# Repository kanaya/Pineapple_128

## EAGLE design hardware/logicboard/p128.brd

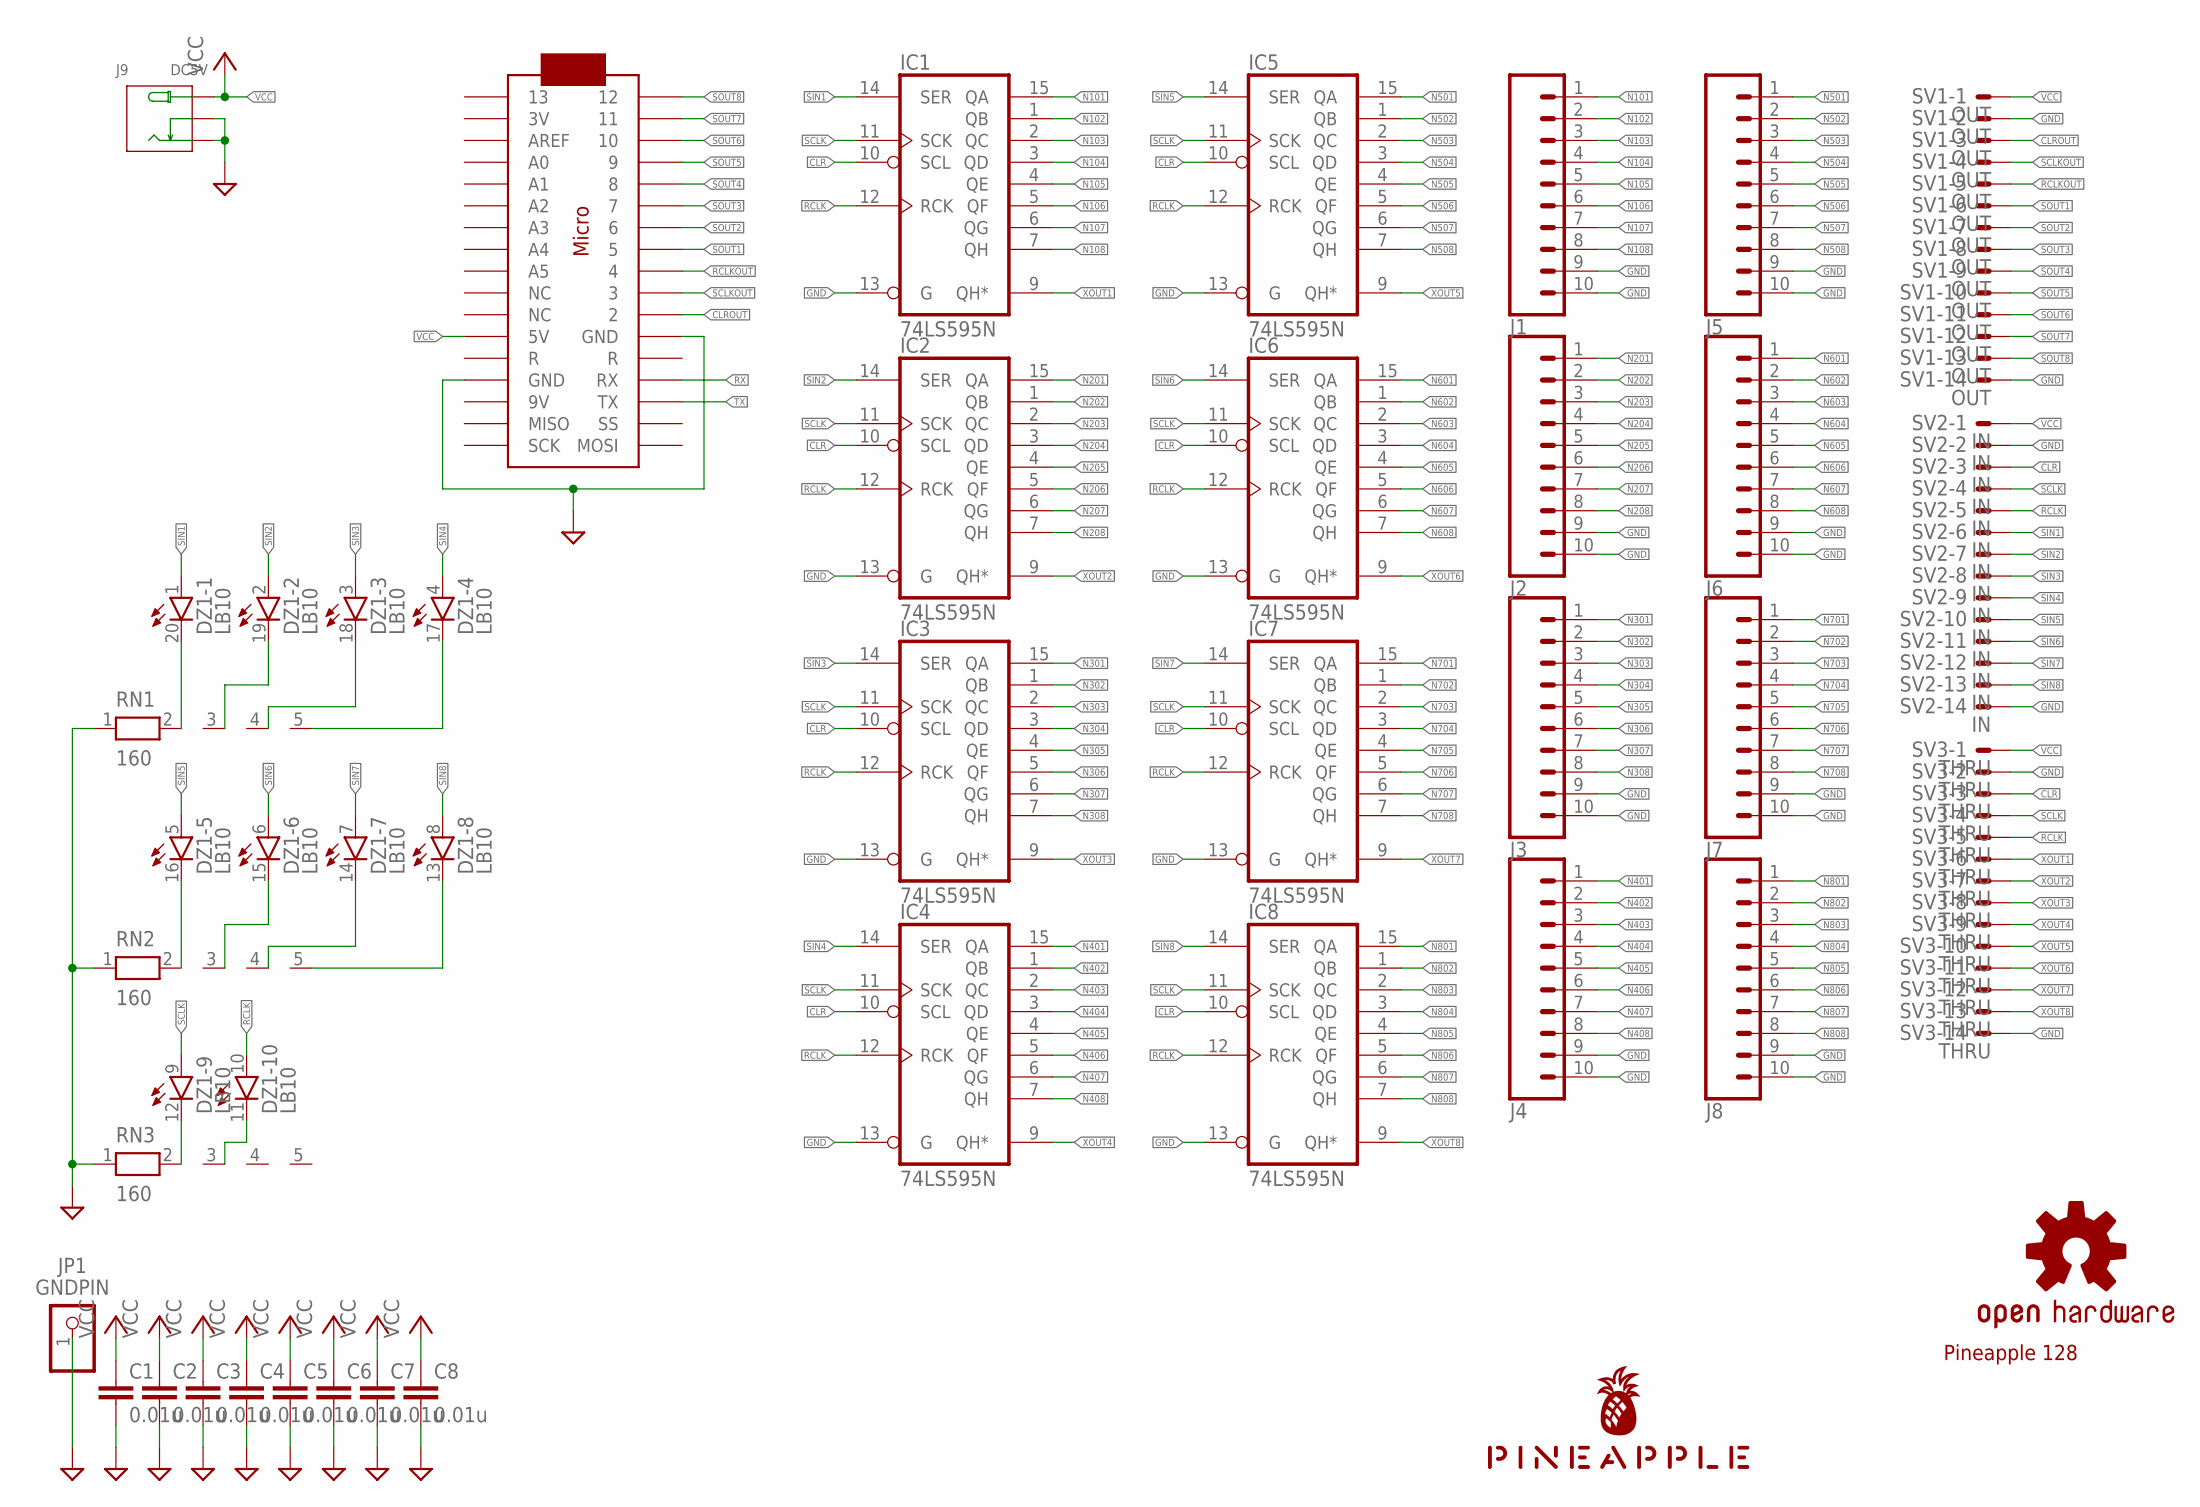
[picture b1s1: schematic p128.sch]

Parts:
C1, C2, C3, C4, C5, C6, C7, C8: 0.01u; C025-024X044
DZ1: LB10
IC1, IC2, IC3, IC4, IC5, IC6, IC7, IC8: 74LS595N; DIL16
J1, J2, J3, J4, J5, J6, J7, J8: CONN_10"; 1X10
J9: DC5V; 3P-L14.2*W11.0*H9.0MM
JP1: GNDPIN; 1X01
LOGO1: OSHW-LOGOS-COPPER; OSHW-LOGO-S_COPPER
RN1, RN2, RN3: 160; RN-5
SV1: OUT; ML14
SV2: IN; ML14
SV3: THRU; ML14
U$1: PINEAPPLE450_SILK
U$2: ARDUINOMICRO

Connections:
CLR: IC1.10 (SCL), IC2.10 (SCL), IC3.10 (SCL), IC4.10 (SCL), IC5.10 (SCL), IC6.10 (SCL), IC7.10 (SCL), IC8.10 (SCL), SV2.3, SV3.3
CLROUT: SV1.3, U$2.P$11 (2)
GND: C1.2, C2.2, C3.2, C4.2, C5.2, C6.2, C7.2, C8.2, IC1.8 (GND), IC1.13 (G), IC2.8 (GND), IC2.13 (G), IC3.8 (GND), IC3.13 (G), IC4.8 (GND), IC4.13 (G), IC5.8 (GND), IC5.13 (G), IC6.8 (GND), IC6.13 (G), IC7.8 (GND), IC7.13 (G), IC8.8 (GND), IC8.13 (G), J1.9, J1.10, J2.9, J2.10, J3.9, J3.10, J4.9, J4.10, J5.9, J5.10, J6.9, J6.10, J7.9, J7.10, J8.9, J8.10, J9.-1 (-), J9.-2 (CDN), JP1.1, RN1.1, RN2.1, RN3.1, SV1.2, SV1.14, SV2.2, SV2.14, SV3.2, SV3.14, U$2.P$12 (GND), U$2.P$21 (GND)
N101: IC1.15 (QA), J1.1
N102: IC1.1 (QB), J1.2
N103: IC1.2 (QC), J1.3
N104: IC1.3 (QD), J1.4
N105: IC1.4 (QE), J1.5
N106: IC1.5 (QF), J1.6
N107: IC1.6 (QG), J1.7
N108: IC1.7 (QH), J1.8
N201: IC2.15 (QA), J2.1
N202: IC2.1 (QB), J2.2
N203: IC2.2 (QC), J2.3
N204: IC2.3 (QD), J2.4
N205: IC2.4 (QE), J2.5
N206: IC2.5 (QF), J2.6
N207: IC2.6 (QG), J2.7
N208: IC2.7 (QH), J2.8
N301: IC3.15 (QA), J3.1
N302: IC3.1 (QB), J3.2
N303: IC3.2 (QC), J3.3
N304: IC3.3 (QD), J3.4
N305: IC3.4 (QE), J3.5
N306: IC3.5 (QF), J3.6
N307: IC3.6 (QG), J3.7
N308: IC3.7 (QH), J3.8
N401: IC4.15 (QA), J4.1
N402: IC4.1 (QB), J4.2
N403: IC4.2 (QC), J4.3
N404: IC4.3 (QD), J4.4
N405: IC4.4 (QE), J4.5
N406: IC4.5 (QF), J4.6
N407: IC4.6 (QG), J4.7
N408: IC4.7 (QH), J4.8
N501: IC5.15 (QA), J5.1
N502: IC5.1 (QB), J5.2
N503: IC5.2 (QC), J5.3
N504: IC5.3 (QD), J5.4
N505: IC5.4 (QE), J5.5
N506: IC5.5 (QF), J5.6
N507: IC5.6 (QG), J5.7
N508: IC5.7 (QH), J5.8
N601: IC6.15 (QA), J6.1
N602: IC6.1 (QB), J6.2
N603: IC6.2 (QC), J6.3
N604: IC6.3 (QD), J6.4
N605: IC6.4 (QE), J6.5
N606: IC6.5 (QF), J6.6
N607: IC6.6 (QG), J6.7
N608: IC6.7 (QH), J6.8
N701: IC7.15 (QA), J7.1
N702: IC7.1 (QB), J7.2
N703: IC7.2 (QC), J7.3
N704: IC7.3 (QD), J7.4
N705: IC7.4 (QE), J7.5
N706: IC7.5 (QF), J7.6
N707: IC7.6 (QG), J7.7
N708: IC7.7 (QH), J7.8
N801: IC8.15 (QA), J8.1
N802: IC8.1 (QB), J8.2
N803: IC8.2 (QC), J8.3
N804: IC8.3 (QD), J8.4
N805: IC8.4 (QE), J8.5
N806: IC8.5 (QF), J8.6
N807: IC8.6 (QG), J8.7
N808: IC8.7 (QH), J8.8
unnamed: DZ1.20 (C), RN1.2
unnamed: DZ1.19 (C), RN1.3
unnamed: DZ1.18 (C), RN1.4
unnamed: DZ1.17 (C), RN1.5
unnamed: DZ1.16 (C), RN2.2
unnamed: DZ1.15 (C), RN2.3
unnamed: DZ1.14 (C), RN2.4
unnamed: DZ1.13 (C), RN2.5
unnamed: DZ1.12 (C), RN3.2
unnamed: DZ1.11 (C), RN3.3
RCLK: DZ1.10 (A), IC1.12 (RCK), IC2.12 (RCK), IC3.12 (RCK), IC4.12 (RCK), IC5.12 (RCK), IC6.12 (RCK), IC7.12 (RCK), IC8.12 (RCK), SV2.5, SV3.5
RCLKOUT: SV1.5, U$2.P$9 (4)
RX: U$2.P$14 (RX)
SCLK: DZ1.9 (A), IC1.11 (SCK), IC2.11 (SCK), IC3.11 (SCK), IC4.11 (SCK), IC5.11 (SCK), IC6.11 (SCK), IC7.11 (SCK), IC8.11 (SCK), SV2.4, SV3.4
SCLKOUT: SV1.4, U$2.P$10 (3)
SIN1: DZ1.1 (A), IC1.14 (SER), SV2.6
SIN2: DZ1.2 (A), IC2.14 (SER), SV2.7
SIN3: DZ1.3 (A), IC3.14 (SER), SV2.8
SIN4: DZ1.4 (A), IC4.14 (SER), SV2.9
SIN5: DZ1.5 (A), IC5.14 (SER), SV2.10
SIN6: DZ1.6 (A), IC6.14 (SER), SV2.11
SIN7: DZ1.7 (A), IC7.14 (SER), SV2.12
SIN8: DZ1.8 (A), IC8.14 (SER), SV2.13
SOUT1: SV1.6, U$2.P$8 (5)
SOUT2: SV1.7, U$2.P$7 (6)
SOUT3: SV1.8, U$2.P$6 (7)
SOUT4: SV1.9, U$2.P$5 (8)
SOUT5: SV1.10, U$2.P$4 (9)
SOUT6: SV1.11, U$2.P$3 (10)
SOUT7: SV1.12, U$2.P$2 (11)
SOUT8: SV1.13, U$2.P$1 (12)
TX: U$2.P$15 (TX)
VCC: C1.1, C2.1, C3.1, C4.1, C5.1, C6.1, C7.1, C8.1, IC1.16 (VCC), IC2.16 (VCC), IC3.16 (VCC), IC4.16 (VCC), IC5.16 (VCC), IC6.16 (VCC), IC7.16 (VCC), IC8.16 (VCC), J9.+, SV1.1, SV2.1, SV3.1, U$2.P$23 (5V)
XOUT1: IC1.9 (QH*), SV3.6
XOUT2: IC2.9 (QH*), SV3.7
XOUT3: IC3.9 (QH*), SV3.8
XOUT4: IC4.9 (QH*), SV3.9
XOUT5: IC5.9 (QH*), SV3.10
XOUT6: IC6.9 (QH*), SV3.11
XOUT7: IC7.9 (QH*), SV3.12
XOUT8: IC8.9 (QH*), SV3.13

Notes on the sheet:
Pineapple 128

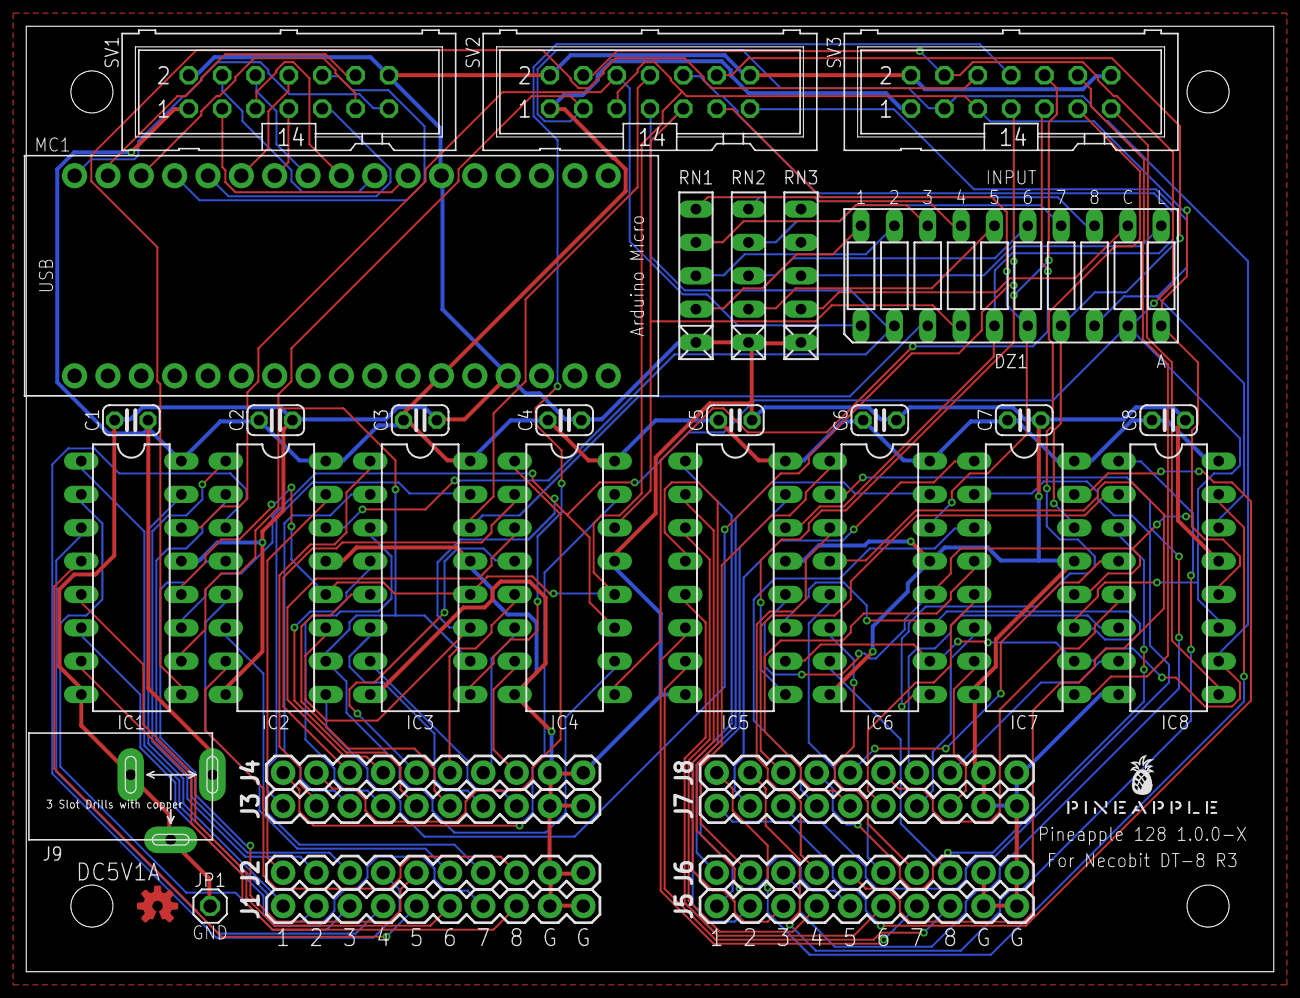
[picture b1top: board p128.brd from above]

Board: 2 copper layers, 94.9 x 71.9 mm, 36 parts (0 on the bottom side), 106 nets.

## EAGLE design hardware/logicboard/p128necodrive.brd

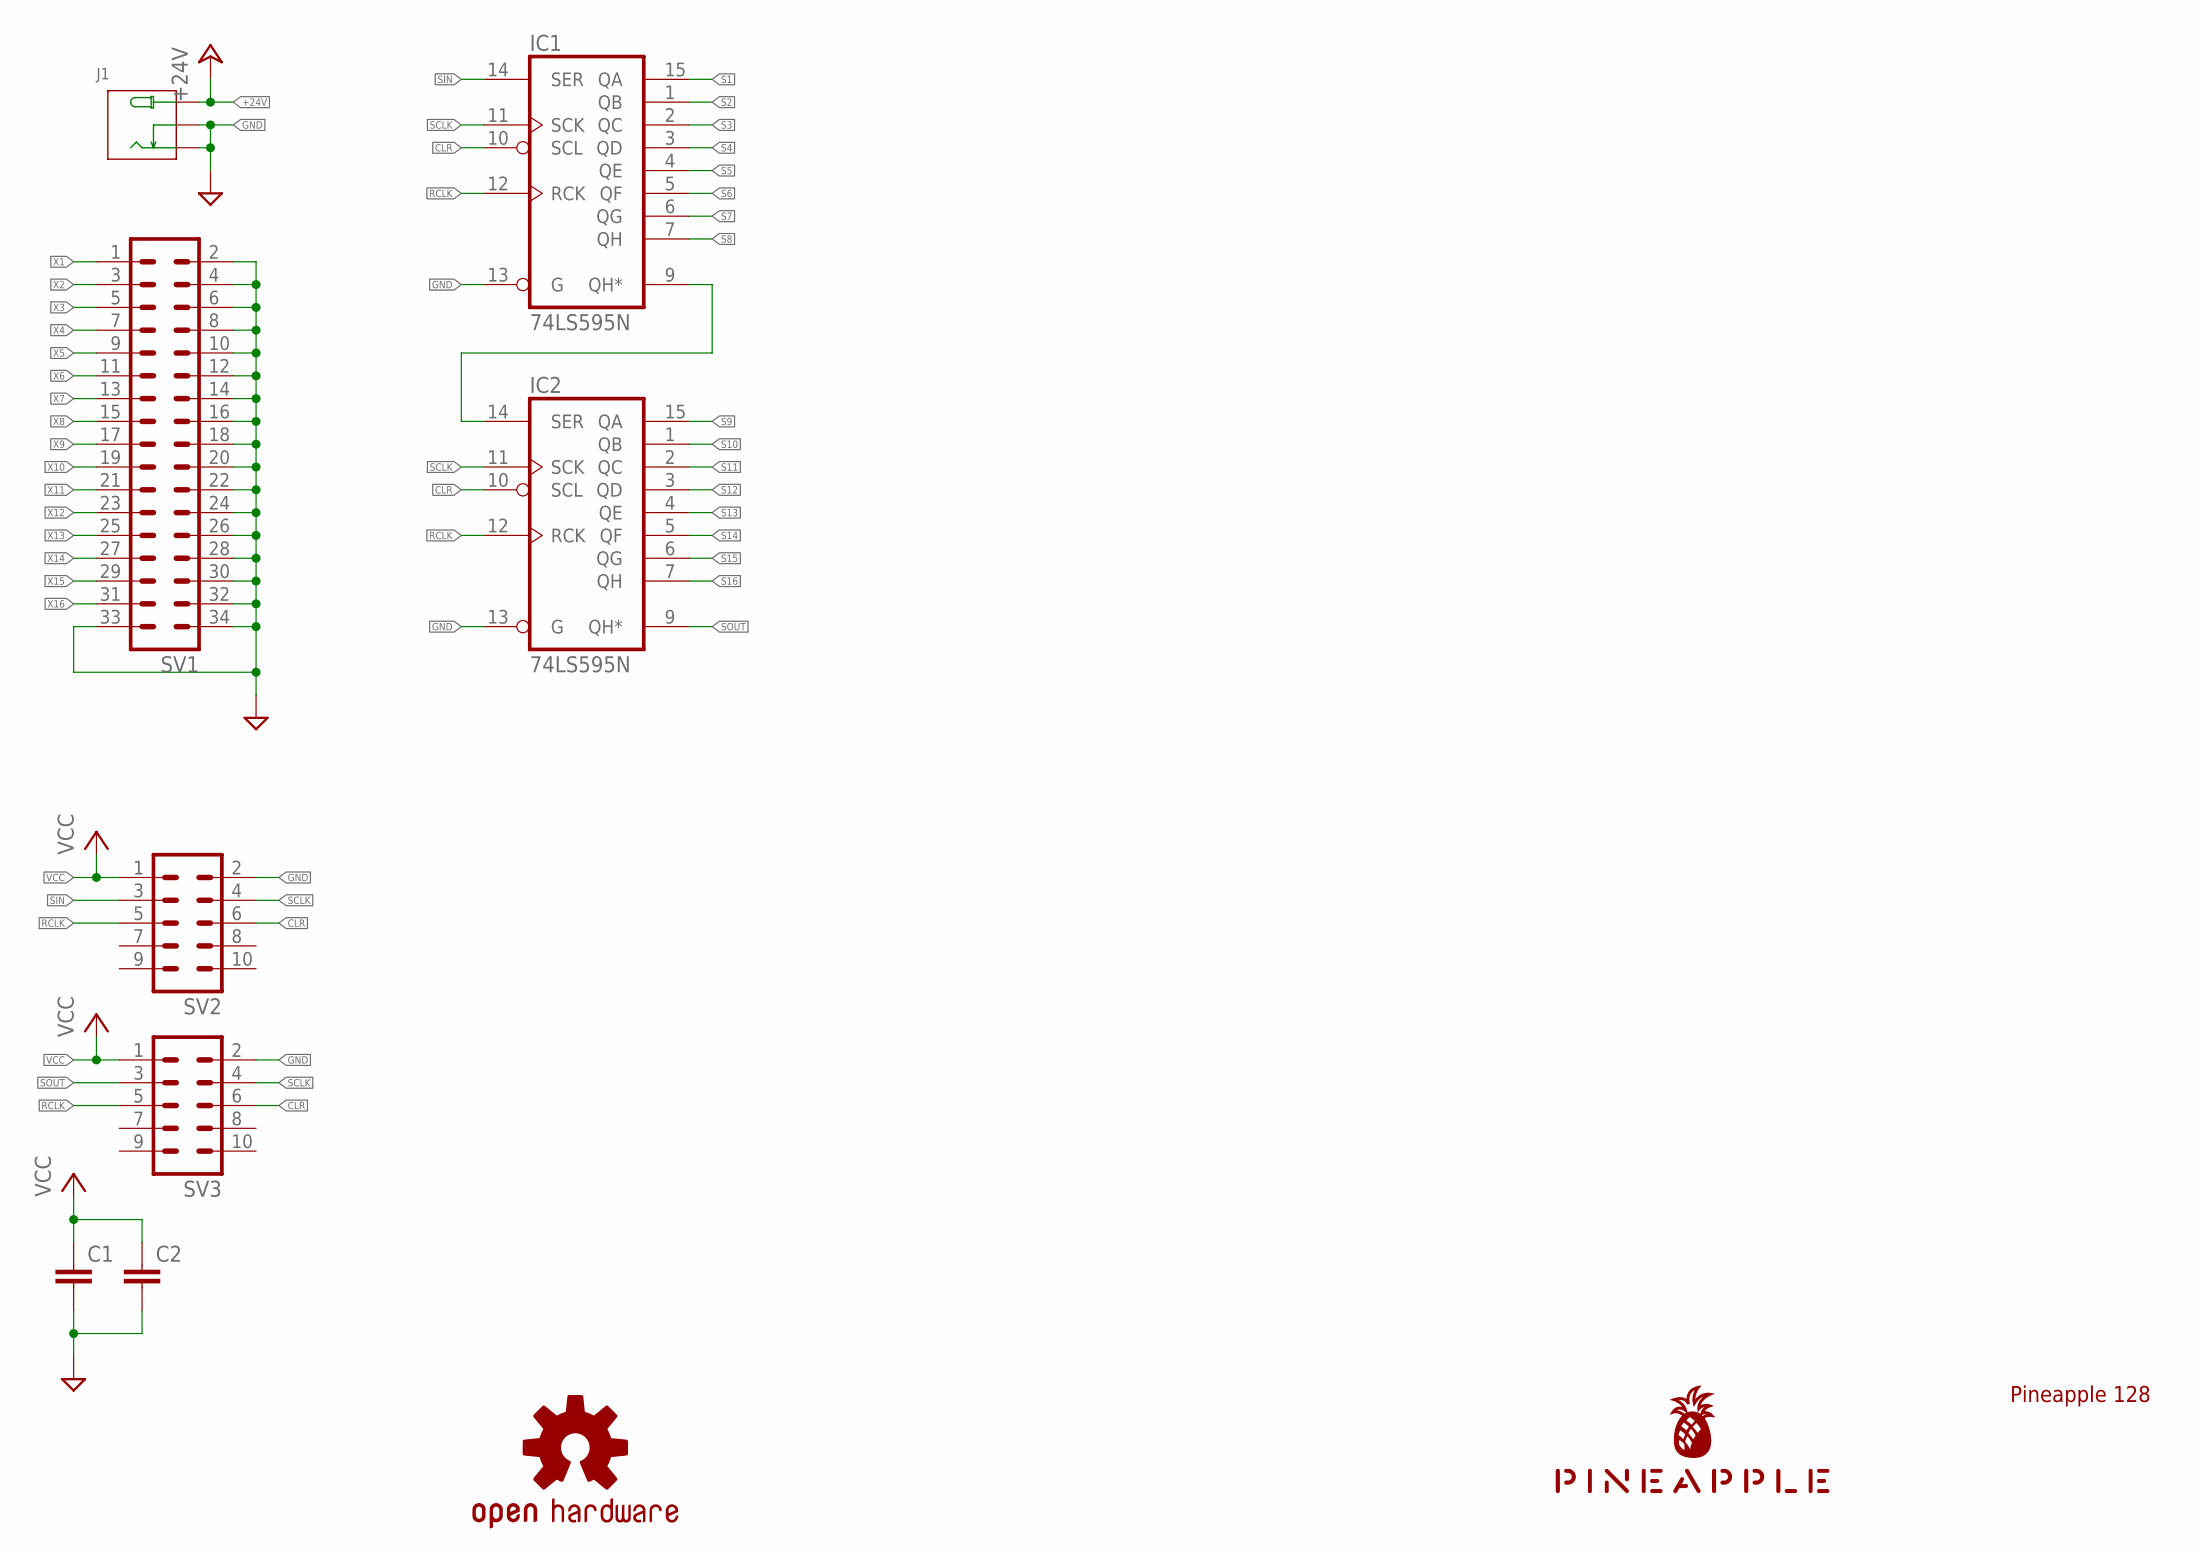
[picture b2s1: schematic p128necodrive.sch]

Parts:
C1, C2: C-EU025-024X044; C025-024X044
IC1, IC2: 74LS595N; DIL16
J1: JACK-DC-005'DC-005'; 3P-L14.2*W11.0*H9.0MM
LOGO1: OSHW-LOGOS-COPPER; OSHW-LOGO-S_COPPER
SV1: ML34L
SV2, SV3: ML10L
U$1: PINEAPPLE450_SILK

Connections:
+24V: J1.+
CLR: IC1.10 (SCL), IC2.10 (SCL), SV2.6, SV3.6
GND: C1.2, C2.2, IC1.8 (GND), IC1.13 (G), IC2.8 (GND), IC2.13 (G), J1.-1 (-), J1.-2 (CDN), SV1.2, SV1.4, SV1.6, SV1.8, SV1.10, SV1.12, SV1.14, SV1.16, SV1.18, SV1.20, SV1.22, SV1.24, SV1.26, SV1.28, SV1.30, SV1.32, SV1.33, SV1.34, SV2.2, SV3.2
unnamed: IC1.9 (QH*), IC2.14 (SER)
RCLK: IC1.12 (RCK), IC2.12 (RCK), SV2.5, SV3.5
S1: IC1.15 (QA)
S2: IC1.1 (QB)
S3: IC1.2 (QC)
S4: IC1.3 (QD)
S5: IC1.4 (QE)
S6: IC1.5 (QF)
S7: IC1.6 (QG)
S8: IC1.7 (QH)
S9: IC2.15 (QA)
S10: IC2.1 (QB)
S11: IC2.2 (QC)
S12: IC2.3 (QD)
S13: IC2.4 (QE)
S14: IC2.5 (QF)
S15: IC2.6 (QG)
S16: IC2.7 (QH)
SCLK: IC1.11 (SCK), IC2.11 (SCK), SV2.4, SV3.4
SIN: IC1.14 (SER), SV2.3
SOUT: IC2.9 (QH*), SV3.3
VCC: C1.1, C2.1, IC1.16 (VCC), IC2.16 (VCC), SV2.1, SV3.1
X1: SV1.1
X2: SV1.3
X3: SV1.5
X4: SV1.7
X5: SV1.9
X6: SV1.11
X7: SV1.13
X8: SV1.15
X9: SV1.17
X10: SV1.19
X11: SV1.21
X12: SV1.23
X13: SV1.25
X14: SV1.27
X15: SV1.29
X16: SV1.31

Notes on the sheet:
Pineapple 128

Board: 2 copper layers, 10 parts (0 on the bottom side), 8 nets, no tracks yet.

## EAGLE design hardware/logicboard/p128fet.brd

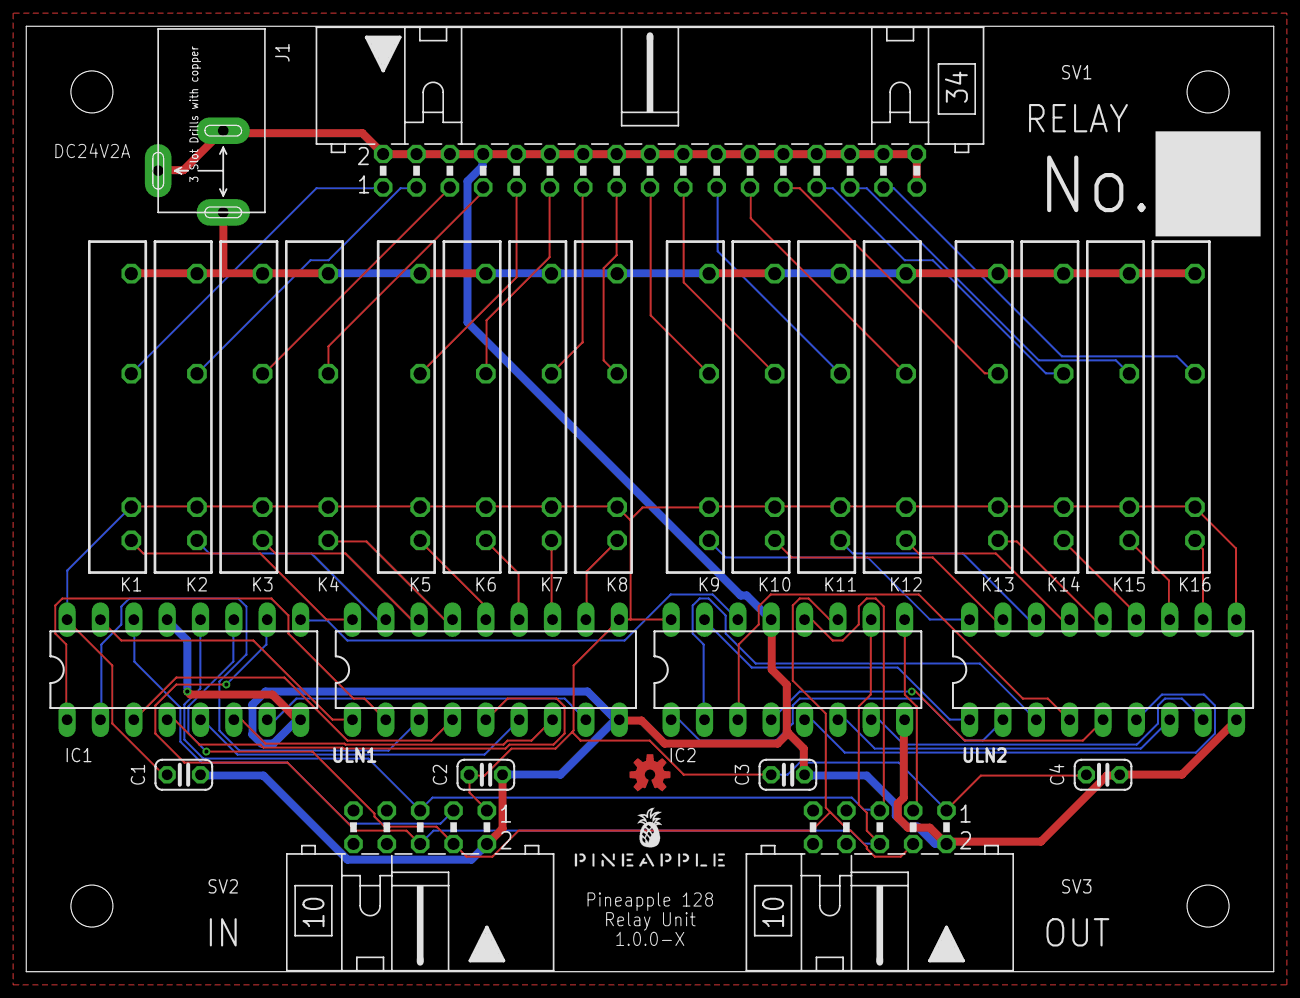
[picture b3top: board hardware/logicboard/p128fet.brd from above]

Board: 2 copper layers, 94.9 x 71.9 mm, 30 parts (0 on the bottom side), 57 nets.

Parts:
C1, C2, C3, C4: C025-024X044
IC1, IC2: 74LS595N; DIL16
J1: 3P-L14.2*W11.0*H9.0MM
K1, K2, K3, K4, K5, K6, K7, K8, K9, K10, K11, K12, K13, K14, K15, K16: AQG12105; AQG
LOGO1: OSHW-LOGOS-COPPER; OSHW-LOGO-S_COPPER
SV1: ML34L
SV2, SV3: ML10L
U$1: PINEAPPLE450_SILK
ULN1, ULN2: DIL18

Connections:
+24V: J1.+, K1.O2, K2.O2, K3.O2, K4.O2, K5.O2, K6.O2, K7.O2, K8.O2, K9.O2, K10.O2, K11.O2, K12.O2, K13.O2, K14.O2, K15.O2, K16.O2
CLR: IC1.10, IC2.10, SV2.6, SV3.6
GND: C1.2, C2.2, C3.2, C4.2, IC1.8, IC1.13, IC2.8, IC2.13, J1.-1, J1.-2, SV1.2, SV1.4, SV1.6, SV1.8, SV1.10, SV1.12, SV1.14, SV1.16, SV1.18, SV1.20, SV1.22, SV1.24, SV1.26, SV1.28, SV1.30, SV1.32, SV1.33, SV1.34, SV2.2, SV3.2, ULN1.9, ULN2.9
unnamed: IC1.9, IC2.14
R1: K1.-, ULN1.18
R2: K2.-, ULN1.17
R3: K3.-, ULN1.16
R4: K4.-, ULN1.15
R5: K5.-, ULN1.14
R6: K6.-, ULN1.13
R7: K7.-, ULN1.12
R8: K8.-, ULN1.11
R9: K9.-, ULN2.18
R10: K10.-, ULN2.17
R11: K11.-, ULN2.16
R12: K12.-, ULN2.15
R13: K13.-, ULN2.14
R14: K14.-, ULN2.13
R15: K15.-, ULN2.12
R16: K16.-, ULN2.11
RCLK: IC1.12, IC2.12, SV2.5, SV3.5
S1: IC1.15, ULN1.1
S2: IC1.1, ULN1.2
S3: IC1.2, ULN1.3
S4: IC1.3, ULN1.4
S5: IC1.4, ULN1.5
S6: IC1.5, ULN1.6
S7: IC1.6, ULN1.7
S8: IC1.7, ULN1.8
S9: IC2.15, ULN2.1
S10: IC2.1, ULN2.2
S11: IC2.2, ULN2.3
S12: IC2.3, ULN2.4
S13: IC2.4, ULN2.5
S14: IC2.5, ULN2.6
S15: IC2.6, ULN2.7
S16: IC2.7, ULN2.8
SCLK: IC1.11, IC2.11, SV2.4, SV3.4
SIN: IC1.14, SV2.3
SOUT: IC2.9, SV3.3
VCC: C1.1, C2.1, C3.1, C4.1, IC1.16, IC2.16, K1.+, K2.+, K3.+, K4.+, K5.+, K6.+, K7.+, K8.+, K9.+, K10.+, K11.+, K12.+, K13.+, K14.+, K15.+, K16.+, SV2.1, SV3.1, ULN1.10, ULN2.10
X1: K1.O1, SV1.1
X2: K2.O1, SV1.3
X3: K3.O1, SV1.5
X4: K4.O1, SV1.7
X5: K5.O1, SV1.9
X6: K6.O1, SV1.11
X7: K7.O1, SV1.13
X8: K8.O1, SV1.15
X9: K9.O1, SV1.17
X10: K10.O1, SV1.19
X11: K11.O1, SV1.21
X12: K12.O1, SV1.23
X13: K13.O1, SV1.25
X14: K14.O1, SV1.27
X15: K15.O1, SV1.29
X16: K16.O1, SV1.31

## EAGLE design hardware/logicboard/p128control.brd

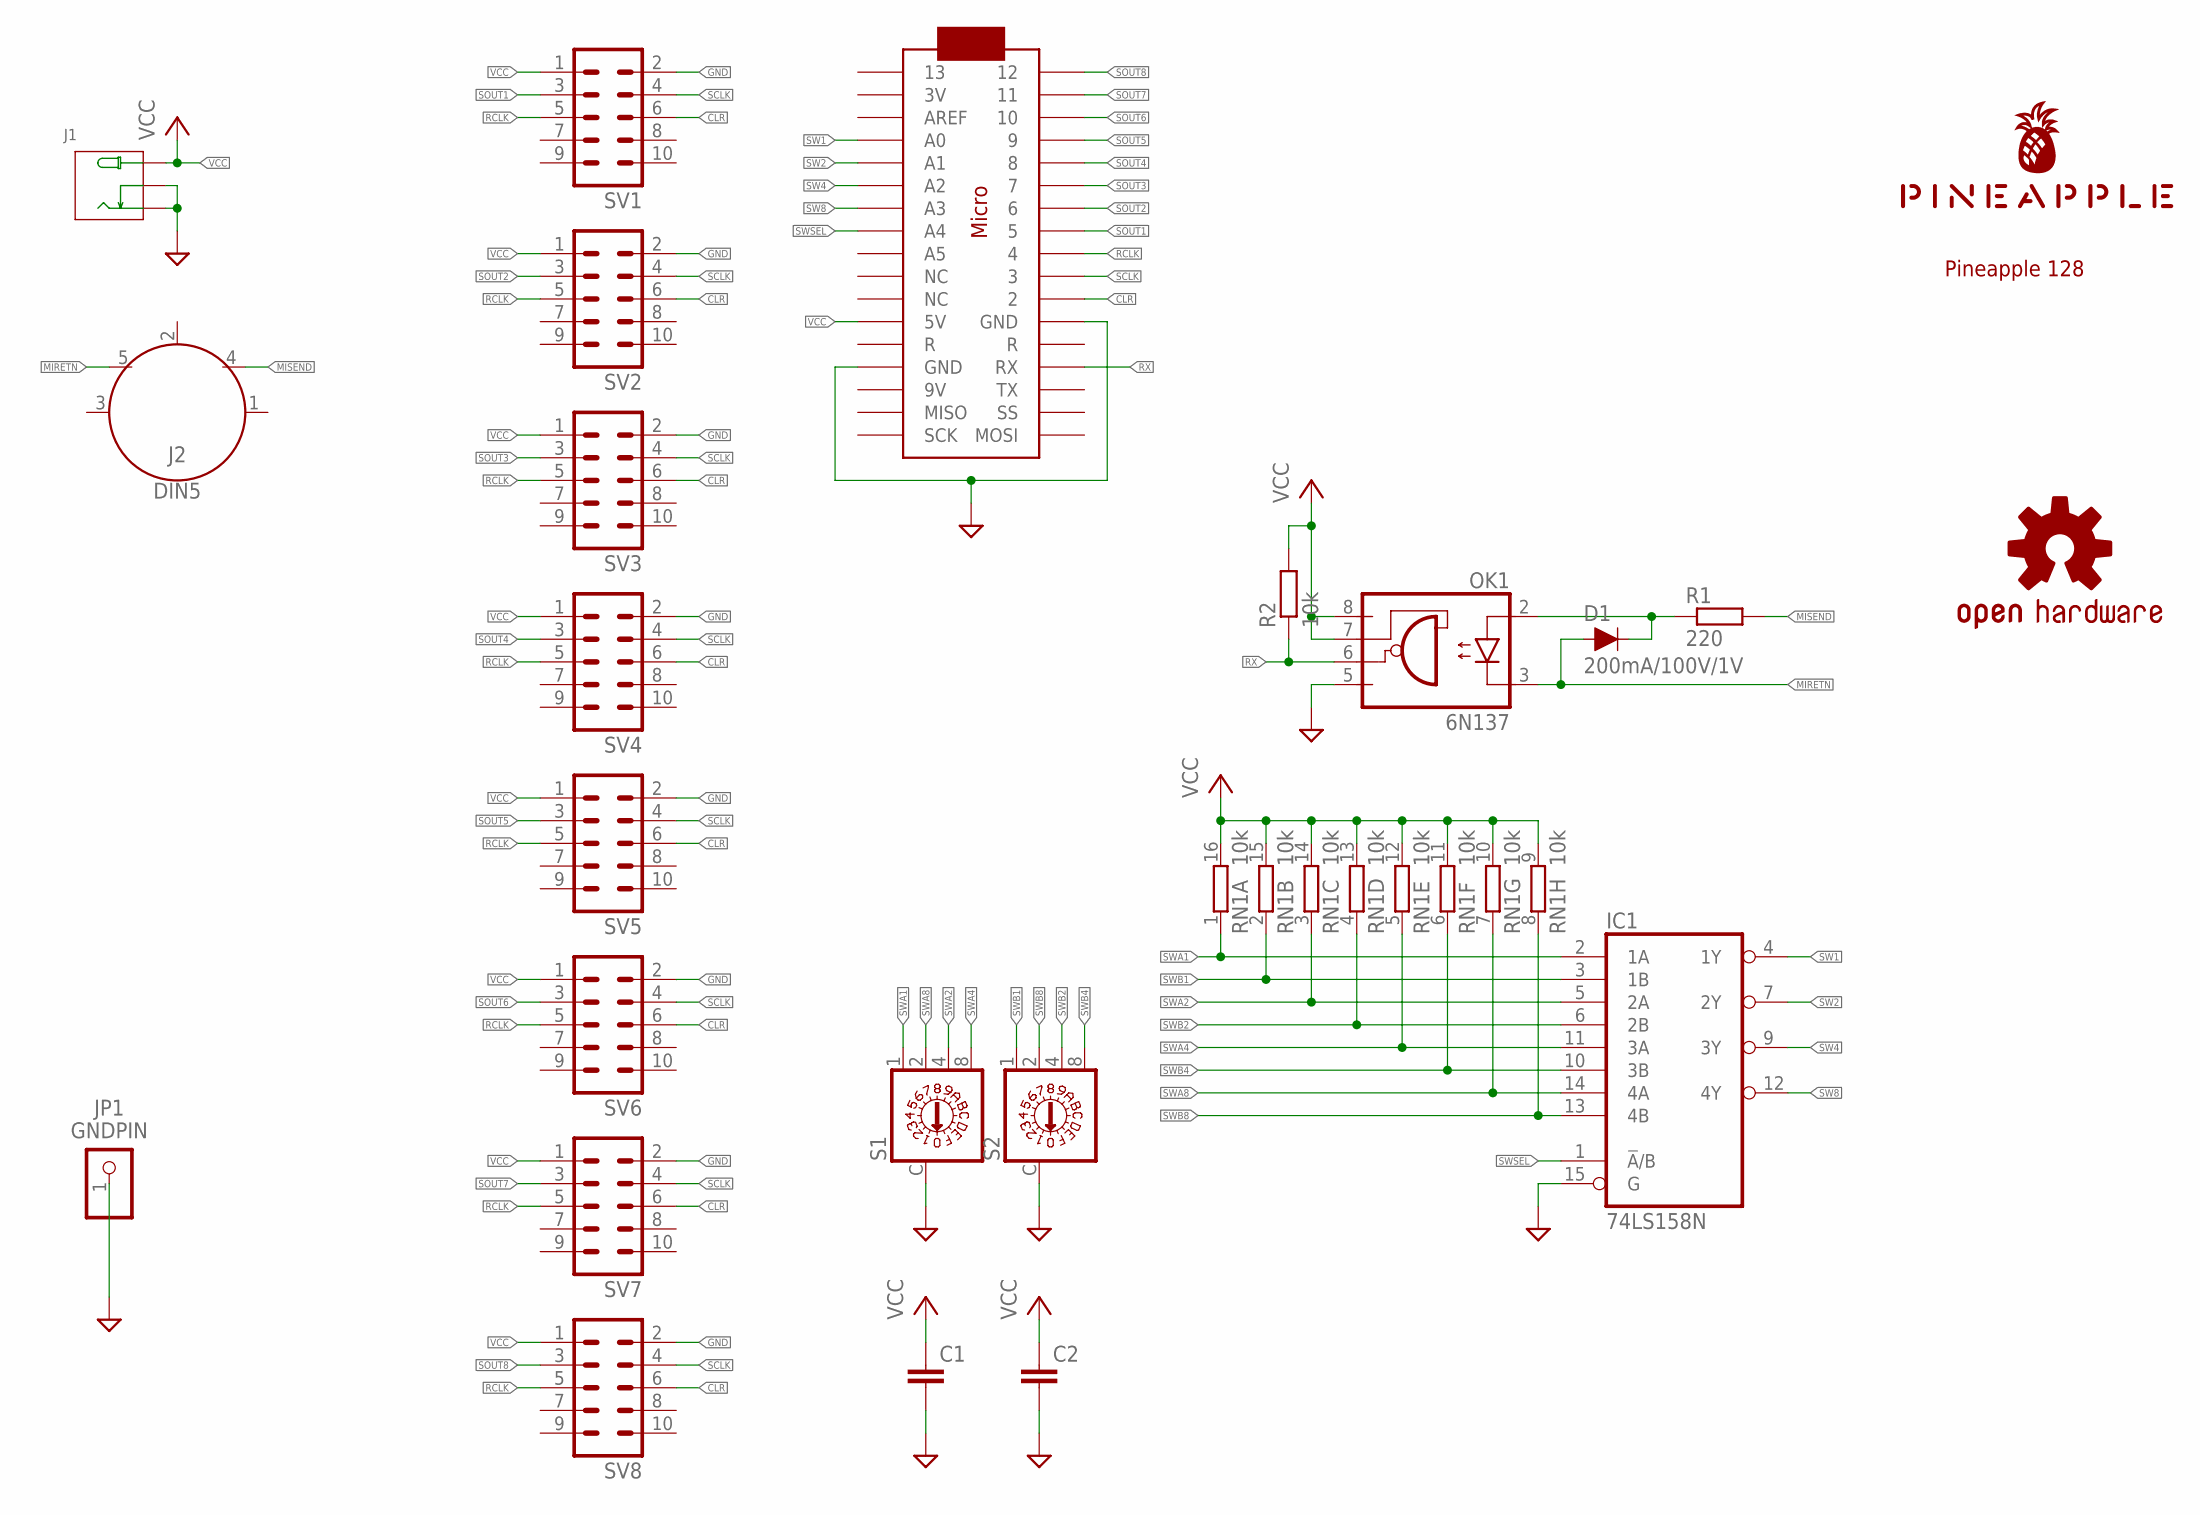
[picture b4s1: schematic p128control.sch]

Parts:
C1, C2: C-EU025-024X044; C025-024X044
D1: 200mA/100V/1V; DIODE-1N4148
IC1: 74LS158N; DIL16
J1: JACK-DC-005'DC-005'; 3P-L14.2*W11.0*H9.0MM
J2: DIN5; DIN5-RA-PTH
JP1: GNDPIN; 1X01
LOGO1: OSHW-LOGOS-COPPER; OSHW-LOGO-S_COPPER
OK1: 6N137; DIL08
R1: 220; 0204/5
R2: 10k; 0204/5
RN1: 10k; DIL16
S1, S2: A1353HEX
SV1, SV2, SV3, SV4, SV5, SV6, SV7, SV8: ML10
U$1: PINEAPPLE450_SILK
U$2: ARDUINOMICRO

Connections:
CLR: SV1.6, SV2.6, SV3.6, SV4.6, SV5.6, SV6.6, SV7.6, SV8.6, U$2.P$11 (2)
GND: C1.2, C2.2, IC1.8 (GND), IC1.15 (G), J1.-1 (-), J1.-2 (CDN), JP1.1, OK1.5 (GND), S1.C, S2.C, SV1.2, SV2.2, SV3.2, SV4.2, SV5.2, SV6.2, SV7.2, SV8.2, U$2.P$12 (GND), U$2.P$21 (GND); also elsewhere on the board
MIRETN: D1.A, J2.5, OK1.3 (C)
MISEND: J2.4, R1.2
unnamed: D1.C, OK1.2 (A), R1.1
RCLK: SV1.5, SV2.5, SV3.5, SV4.5, SV5.5, SV6.5, SV7.5, SV8.5, U$2.P$9 (4)
RX: OK1.6 (VO), R2.1, U$2.P$14 (RX); also elsewhere on the board
SCLK: SV1.4, SV2.4, SV3.4, SV4.4, SV5.4, SV6.4, SV7.4, SV8.4, U$2.P$10 (3)
SOUT1: SV1.3, U$2.P$8 (5)
SOUT2: SV2.3, U$2.P$7 (6)
SOUT3: SV3.3, U$2.P$6 (7)
SOUT4: SV4.3, U$2.P$5 (8)
SOUT5: SV5.3, U$2.P$4 (9)
SOUT6: SV6.3, U$2.P$3 (10)
SOUT7: SV7.3, U$2.P$2 (11)
SOUT8: SV8.3, U$2.P$1 (12)
SW1: IC1.4 (1Y), U$2.P$31 (A0)
SW2: IC1.7 (2Y), U$2.P$30 (A1)
SW4: IC1.9 (3Y), U$2.P$29 (A2)
SW8: IC1.12 (4Y), U$2.P$28 (A3)
SWA1: IC1.2 (1A), RN1.1, S1.1
SWA2: IC1.5 (2A), RN1.3 (1), S1.4
SWA4: IC1.11 (3A), RN1.5 (1), S1.8
SWA8: IC1.14 (4A), RN1.7 (1), S1.2
SWB1: IC1.3 (1B), RN1.2 (1), S2.1
SWB2: IC1.6 (2B), RN1.4 (1), S2.4
SWB4: IC1.10 (3B), RN1.6 (1), S2.8
SWB8: IC1.13 (4B), RN1.8 (1), S2.2
SWSEL: IC1.1 (!A!/B), U$2.P$27 (A4)
TX: U$2.P$15 (TX); also elsewhere on the board
VCC: C1.1, C2.1, IC1.16 (VCC), J1.+, OK1.7 (VE), OK1.8 (VCC), R2.2, RN1.9 (2), RN1.10 (2), RN1.11 (2), RN1.12 (2), RN1.13 (2), RN1.14 (2), RN1.15 (2), RN1.16 (2), SV1.1, SV2.1, SV3.1, SV4.1, SV5.1, SV6.1, SV7.1, SV8.1, U$2.P$23 (5V); also elsewhere on the board

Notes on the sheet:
Pineapple 128

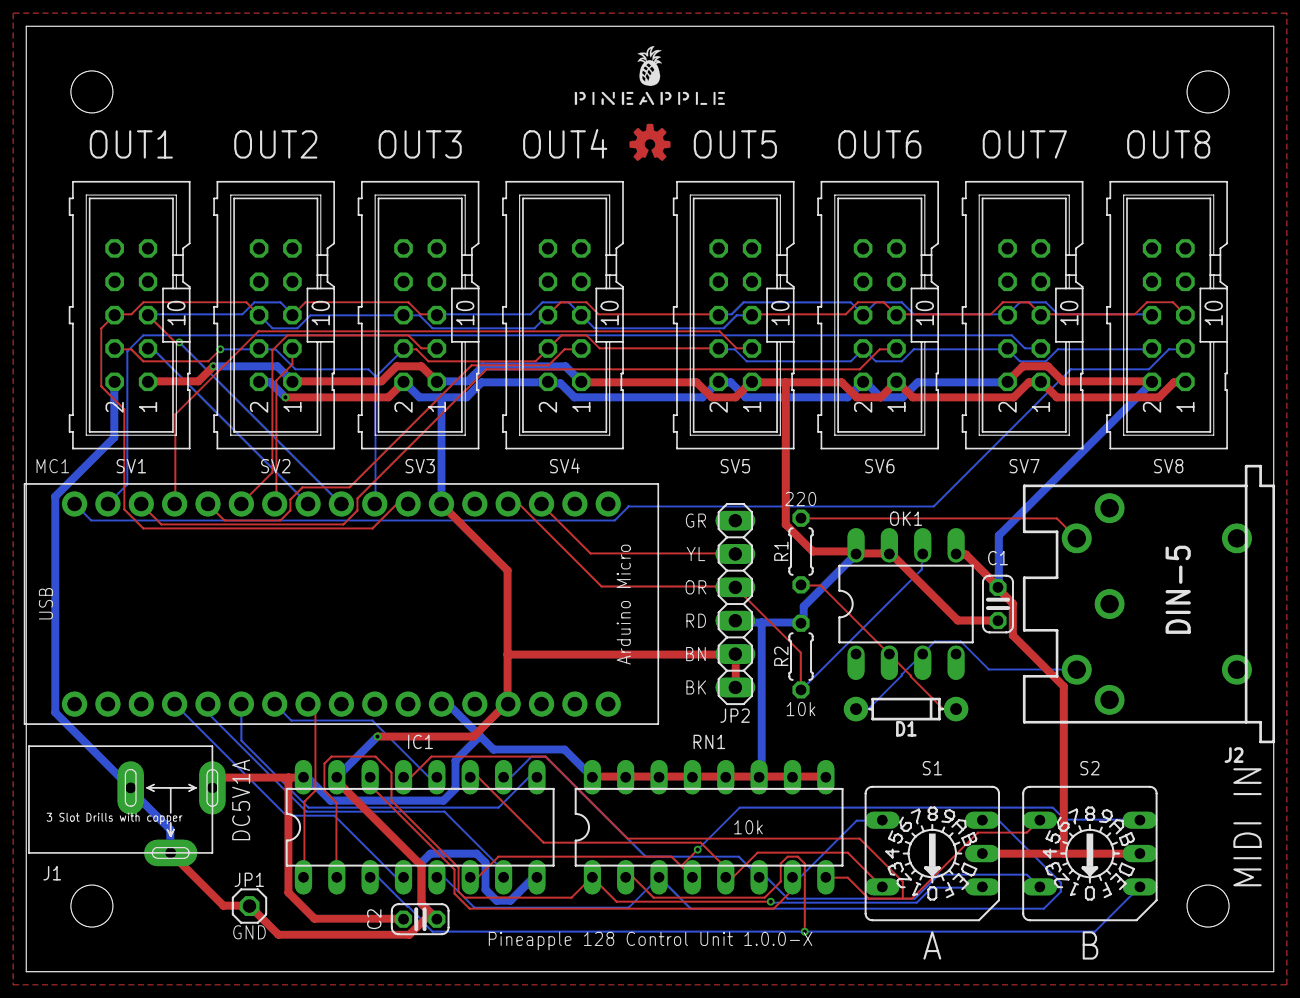
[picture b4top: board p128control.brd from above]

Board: 2 copper layers, 94.9 x 71.9 mm, 25 parts (0 on the bottom side), 31 nets.

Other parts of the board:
JP2: 1X06

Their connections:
GND: JP2.1, JP2.2; also elsewhere on the board
RX: JP2.4; also elsewhere on the board
TX: JP2.5; also elsewhere on the board
VCC: JP2.3; also elsewhere on the board

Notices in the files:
parts and their libraries:
SparkFun-Aesthetics: Licensing: Creative Commons ShareAlike 4.0 International - https://creativecommons.org/licenses/by-sa/4.0
